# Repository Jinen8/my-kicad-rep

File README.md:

# my-kicad-rep
clap switch , ir sensor

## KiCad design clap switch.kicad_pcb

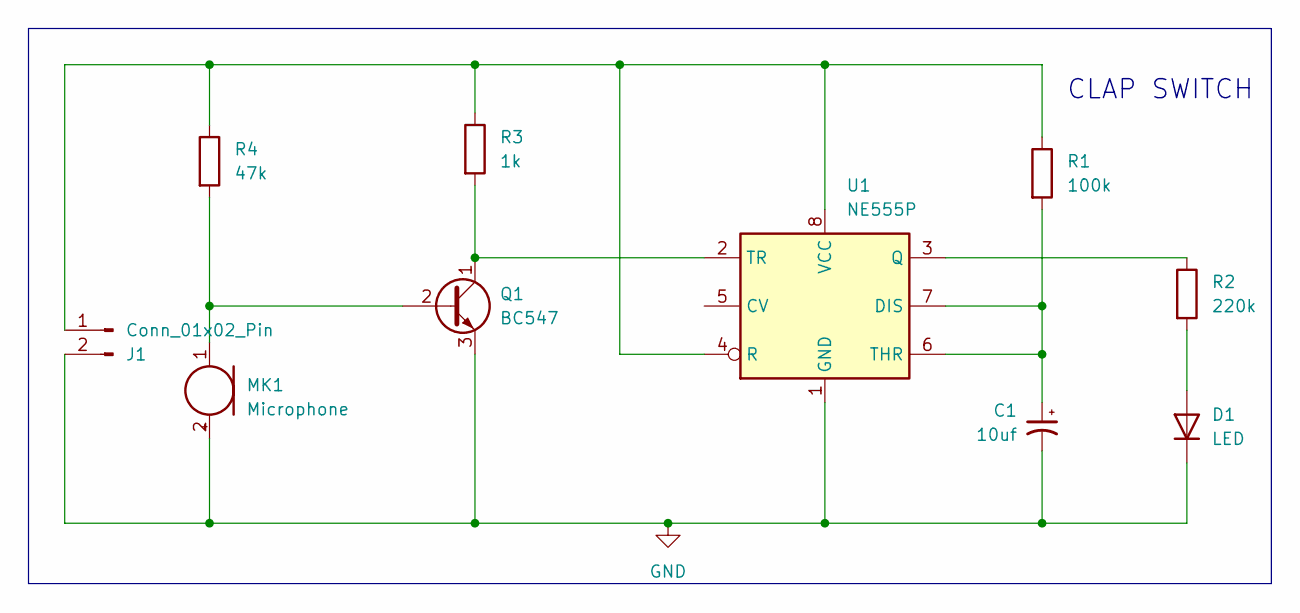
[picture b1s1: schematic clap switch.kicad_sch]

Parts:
C1: 10uf; C_0201_0603Metric
D1: LED; LED_0201_0603Metric_Pad0.64x0.40mm_HandSolder
J1: Conn_01x02_Pin; JWT_A3963_1x02_P3.96mm_Vertical
MK1: Microphone; POM-2244P-C3310-2-R
Q1: BC547; TO-92_Inline
R1: 100k; R_0402_1005Metric_Pad0.72x0.64mm_HandSolder
R2: 220k; R_0402_1005Metric_Pad0.72x0.64mm_HandSolder
R3: 1k; R_0402_1005Metric_Pad0.72x0.64mm_HandSolder
R4: 47k; R_0402_1005Metric_Pad0.72x0.64mm_HandSolder
U1: NE555P; DIP-8_W7.62mm

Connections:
GND: C1.2, D1.1 (K), J1.2, MK1.2 (+), Q1.3 (E), U1.1 (GND)
unnamed: D1.2 (A), R2.2
unnamed: J1.1, R1.1, R3.1, R4.1, U1.4 (R), U1.8 (VCC)
unnamed: MK1.1 (-), Q1.2 (B), R4.2
unnamed: Q1.1 (C), R3.2, U1.2 (TR)
unnamed: C1.1, R1.2, U1.6 (THR), U1.7 (DIS)
unnamed: R2.1, U1.3 (Q)

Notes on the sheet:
CLAP SWITCH

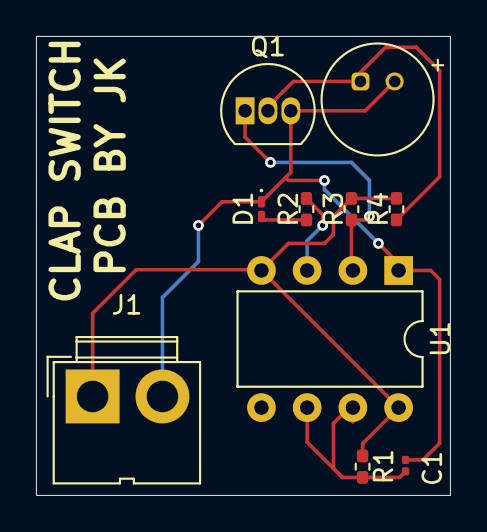
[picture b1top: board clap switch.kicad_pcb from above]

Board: 2 copper layers, 23.0 x 25.5 mm, 10 parts (0 on the bottom side), 7 nets.

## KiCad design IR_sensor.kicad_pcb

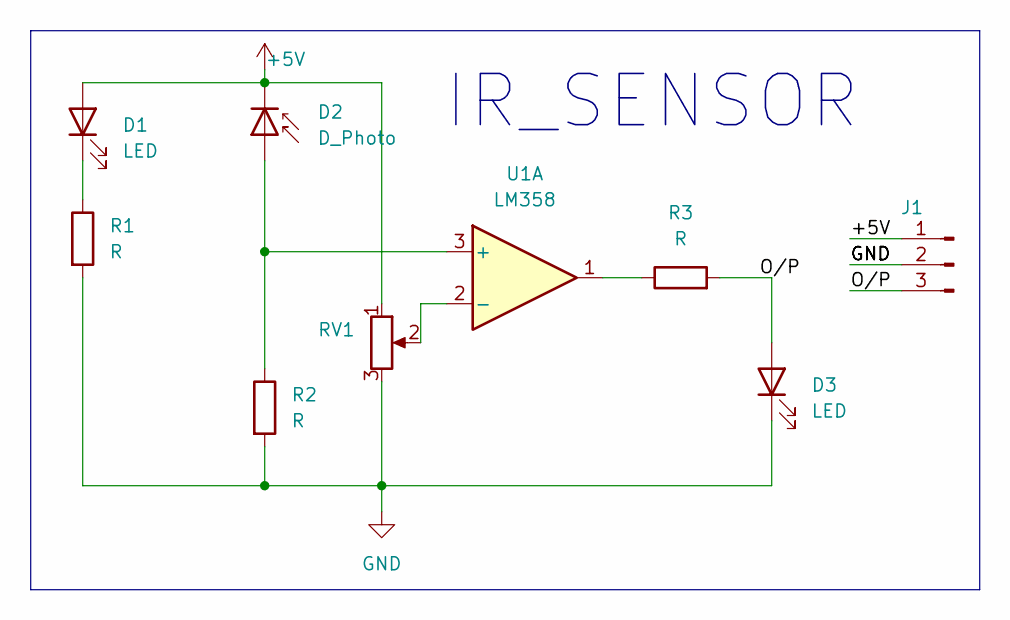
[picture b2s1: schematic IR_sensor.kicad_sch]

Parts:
D1, D3: LED; LED_0402_1005Metric
D2: D_Photo; LED_0402_1005Metric
J1: Conn_01x03_Pin; PinHeader_1x03_P2.54mm_Vertical
R1, R2, R3: R; R_0805_2012Metric
RV1: R_Potentiometer; Potentiometer_ACP_CA9-VSMD_Vertical
U1: LM358; HSOP-8-1EP_3.9x4.9mm_P1.27mm_EP2.41x3.1mm_ThermalVias

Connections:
+5V: D1.2 (A), D2.1 (K), J1.1, RV1.1
/O/P: D3.2 (A), J1.3, R3.2
GND: D3.1 (K), J1.2, R1.2, R2.2, RV1.3
unnamed: D1.1 (K), R1.1
unnamed: D2.2 (A), R2.1, U1.3 (+)
unnamed: R3.1, U1.1
unnamed: RV1.2, U1.2 (-)

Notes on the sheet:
IR_SENSOR

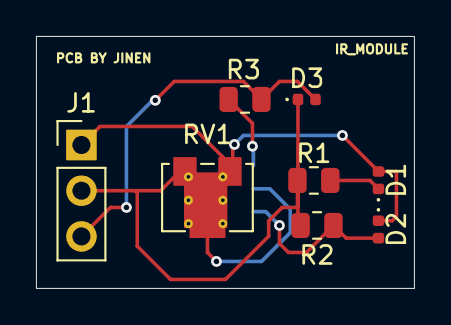
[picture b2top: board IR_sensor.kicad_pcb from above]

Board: 2 copper layers, 21.0 x 14.0 mm, 9 parts (1 on the bottom side), 7 nets.
